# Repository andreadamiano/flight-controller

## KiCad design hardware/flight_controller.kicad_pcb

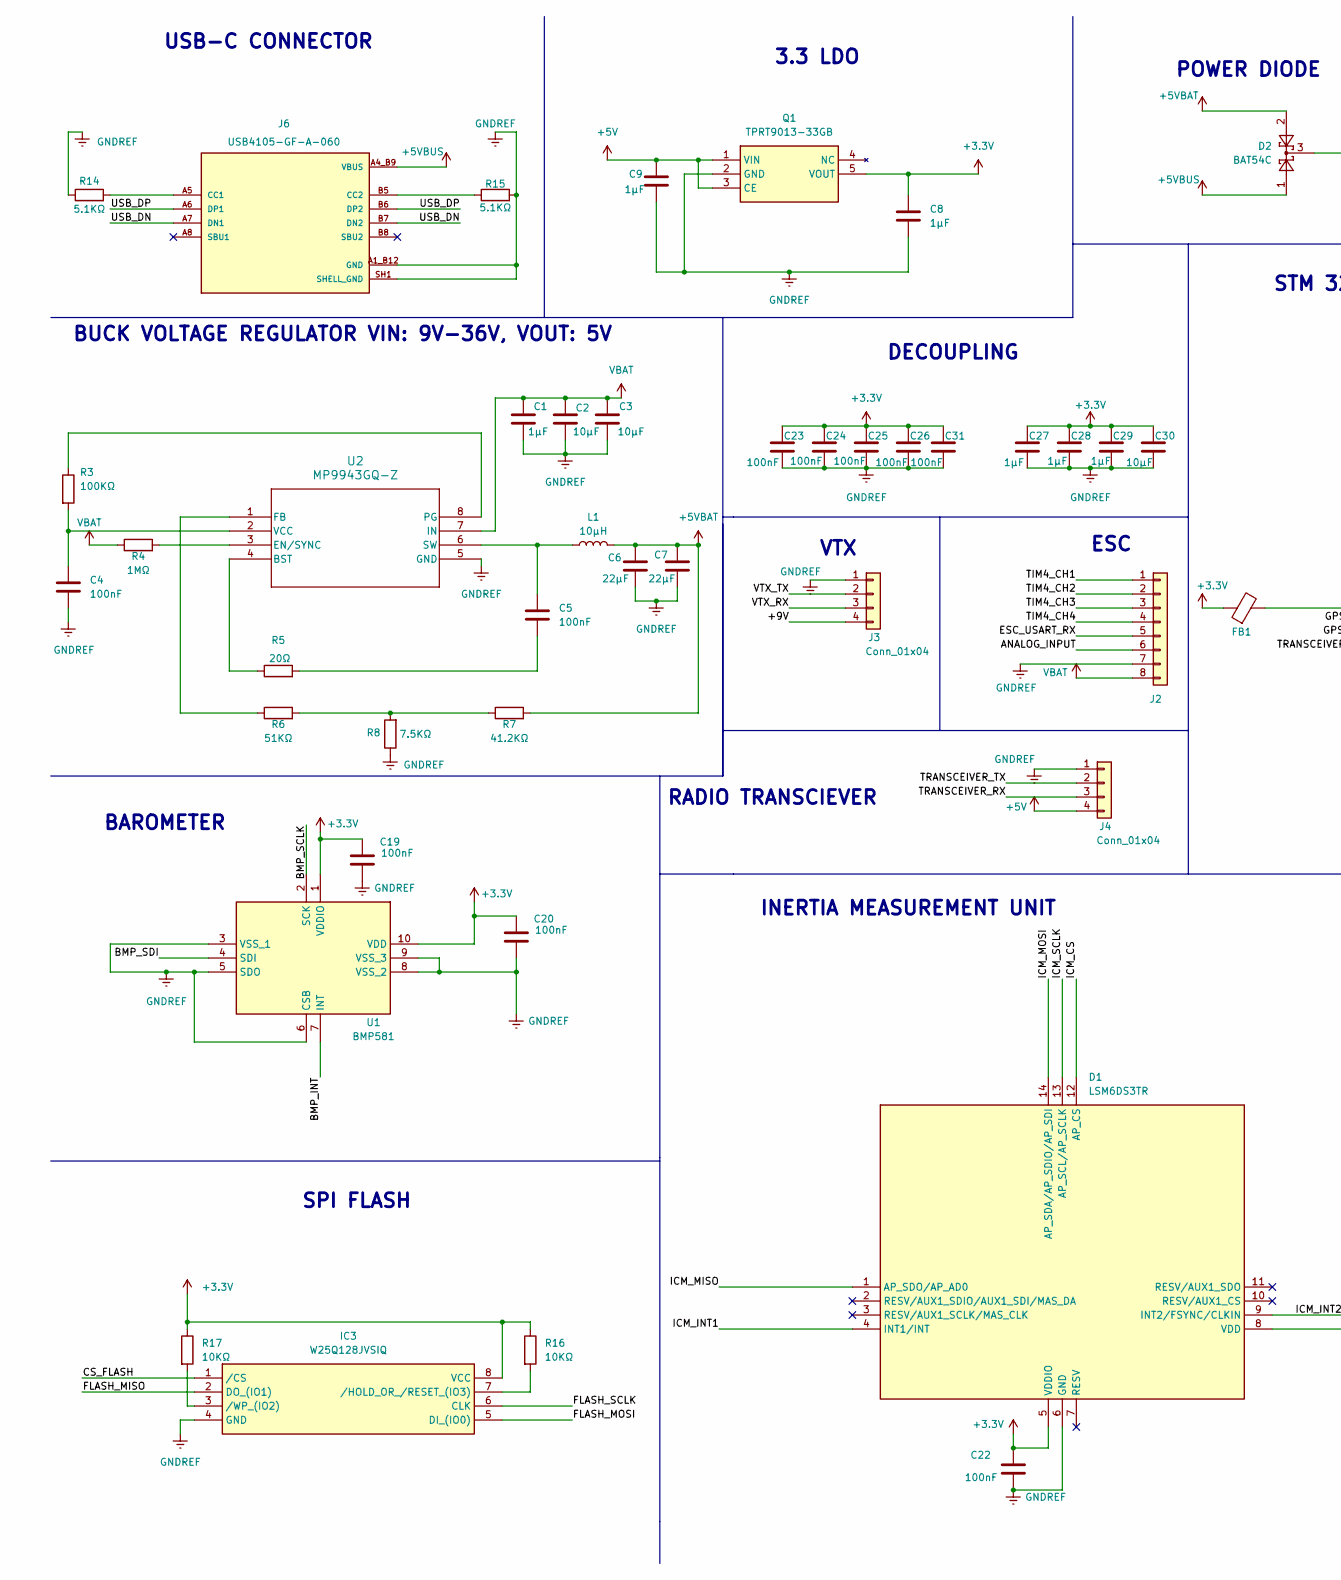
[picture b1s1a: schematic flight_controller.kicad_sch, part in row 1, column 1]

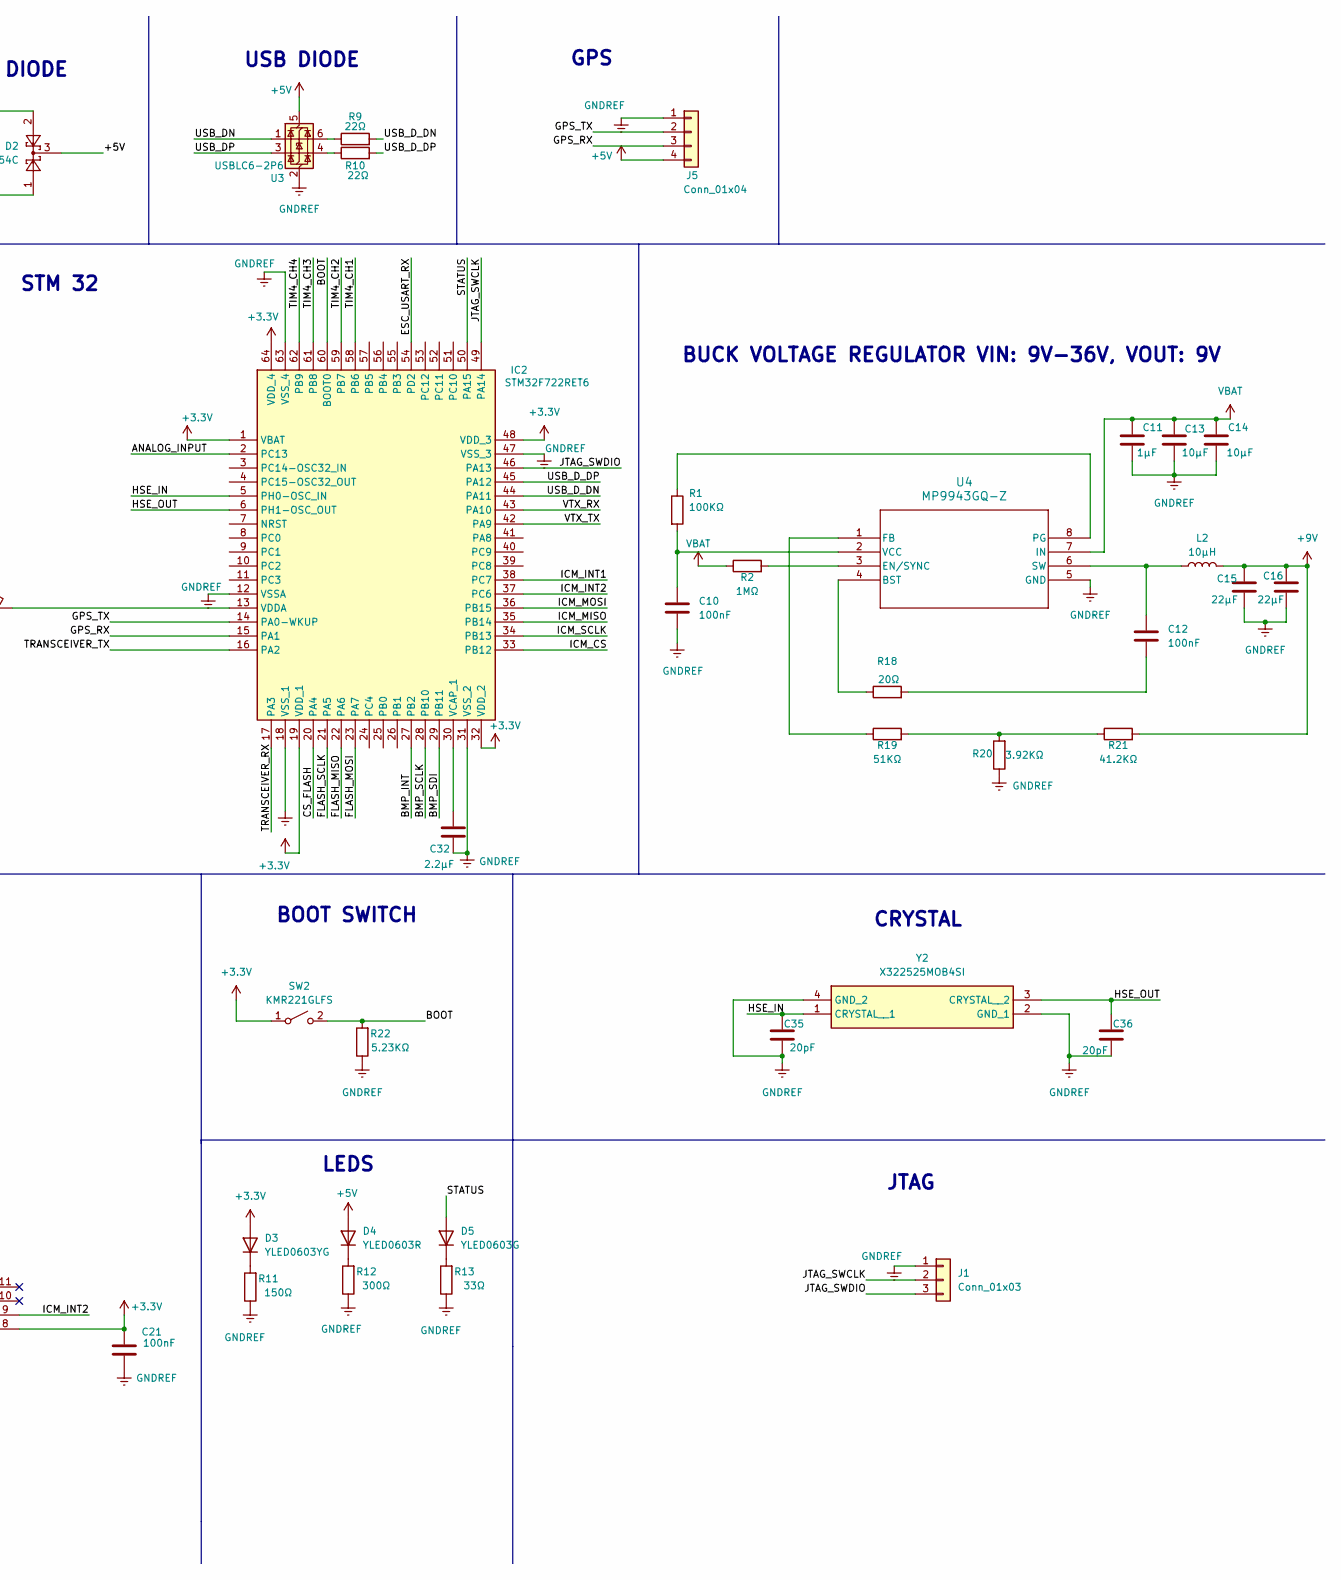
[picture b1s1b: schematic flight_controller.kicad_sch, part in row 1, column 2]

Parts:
C1, C11: 1μF; C_0805_2012Metric
C2, C3, C13, C14, C30: 10μF; C_0805_2012Metric
C4, C5, C10, C12, C19, C20, C21, C22, C23, C24, C25, C26, C31: 100nF; C_0402_1005Metric
C6, C7, C15, C16: 22μF; C_0805_2012Metric
C8, C9, C27, C28, C29: 1μF; C_0603_1608Metric
C32: 2.2μF; C_0603_1608Metric
C35, C36: 20pF; C_0402_1005Metric
D1: LSM6DS3TR; QFN50P300X250X78-14N; Manufacturer_Part_Number ICM-45686
D2: BAT54C; SOT-23
D3: YLED0603YG; LED_0603_1608Metric
D4: YLED0603R; LED_0603_1608Metric
D5: YLED0603G; LED_0603_1608Metric
FB1: FCM1608KF-601T03; L_0603_1608Metric
IC2: STM32F722RET6; QFP50P1200X1200X160-64N; Manufacturer_Part_Number STM32F722RET6; Mouser Part Number 511-STM32F722RET6
IC3: W25Q128JVSIQ; SOIC127P790X216-8N; Manufacturer_Part_Number W25Q128JVSIQ; Mouser Part Number 454-W25Q128JVSIQ
J1: Conn_01x03; PinHeader_1x03_P1.00mm_Vertical
J2: JST SM08B-SRSS-TB(LF)(SN); JST_SH_SM08B-SRSS-TB_1x08-1MP_P1.00mm_Horizontal
J3, J4, J5: Conn_01x04; PinHeader_1x04_P2.54mm_Vertical
J6: USB4105-GF-A-060; GCT_USB4105-GF-A-060; PARTREV B3
L1, L2: 10μH; IND_FXL0530_CMT
Q1: TPRT9013-33GB; SOT95P280X125-5N; Manufacturer_Part_Number TPRT9013-33GB
R1, R3: 100KΩ; R_0402_1005Metric
R2, R4: 1MΩ; R_0603_1608Metric
R5, R18: 20Ω; R_0402_1005Metric
R6, R19: 51KΩ; R_0402_1005Metric
R7, R21: 41.2KΩ; R_0402_1005Metric
R8: 7.5KΩ; R_0402_1005Metric
R9, R10: 22Ω; R_0402_1005Metric
R11: 150Ω; R_0402_1005Metric
R12: 300Ω; R_0402_1005Metric
R13: 33Ω; R_0402_1005Metric
R14, R15: 5.1KΩ; R_0402_1005Metric
R16, R17: 10KΩ; R_0402_1005Metric
R20: 3.92KΩ; R_0402_1005Metric
R22: 5.23KΩ; R_0402_1005Metric
SW2: KMR221GLFS; SW_Push_1P1T-SH_NO_CK_KMR2xxG
U1: BMP581; Manufacturer_Part_Number BMP581; Mouser Part Number 262-BMP581
U2, U4: MP9943GQ-Z; QFN-8_MP9943_MNP
U3: USBLC6-2P6; SOT-666
Y2: X322525MOB4SI; Manufacturer_Part_Number X322525MOB4SI

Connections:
+3.3V: C8.1, C19.1, C20.1, C21.1, C22.1, C23.2, C24.2, C25.2, C26.2, C27.2, C28.2, C29.2, C30.2, C31.2, D1.5 (VDDIO), D1.8 (VDD), D3.2 (A), FB1.1, IC2.1 (VBAT), IC2.19 (VDD_1), IC2.32 (VDD_2), IC2.48 (VDD_3), IC2.64 (VDD_4), IC3.8 (VCC), Q1.5 (VOUT), R16.1, R17.1, SW2.1 (A), U1.1 (VDDIO), U1.10 (VDD)
+5V: C9.1, D2.3, D4.2 (A), J4.4, J5.4, Q1.1 (VIN), Q1.3 (CE), U3.5 (VBUS)
+5VBAT: C6.1, C7.1, D2.2, L1.2, R7.2
+5VBUS: D2.1, J6.A4_B9 (VBUS), J6.B4_A9 (VBUS)
+9V: C15.1, C16.1, J3.4, L2.2, R21.2
/ANALOG_INPUT: IC2.2 (PC13), J2.6
/BMP_INT: IC2.27 (PB2), U1.7 (INT)
/BMP_SCLK: IC2.28 (PB10), U1.2 (SCK)
/BMP_SDI: IC2.29 (PB11), U1.4 (SDI)
/BOOT: IC2.60 (BOOT0), R22.2, SW2.2 (B)
/CS_FLASH: IC2.20 (PA4), IC3.1 (/CS)
/ESC_USART_RX: IC2.54 (PD2), J2.5
/FLASH_MISO: IC2.22 (PA6), IC3.2 (DO_(IO1))
/FLASH_MOSI: IC2.23 (PA7), IC3.5 (DI_(IO0))
/FLASH_SCLK: IC2.21 (PA5), IC3.6 (CLK)
/GPS_RX: IC2.15 (PA1), J5.3
/GPS_TX: IC2.14 (PA0-WKUP), J5.2
/HSE_IN: C35.2, IC2.5 (PH0-OSC_IN), Y2.1 (CRYSTAL__1)
/HSE_OUT: C36.2, IC2.6 (PH1-OSC_OUT), Y2.3 (CRYSTAL__2)
/ICM_CS: D1.12 (AP_CS), IC2.33 (PB12)
/ICM_INT1: D1.4 (INT1/INT), IC2.38 (PC7)
/ICM_INT2: D1.9 (INT2/FSYNC/CLKIN), IC2.37 (PC6)
/ICM_MISO: D1.1 (AP_SDO/AP_AD0), IC2.35 (PB14)
/ICM_MOSI: D1.14 (AP_SDA/AP_SDIO/AP_SDI), IC2.36 (PB15)
/ICM_SCLK: D1.13 (AP_SCL/AP_SCLK), IC2.34 (PB13)
/JTAG_SWCLK: IC2.49 (PA14), J1.2
/JTAG_SWDIO: IC2.46 (PA13), J1.3
/STATUS: D5.2 (A), IC2.50 (PA15)
/TIM4_CH1: IC2.58 (PB6), J2.1
/TIM4_CH2: IC2.59 (PB7), J2.2
/TIM4_CH3: IC2.61 (PB8), J2.3
/TIM4_CH4: IC2.62 (PB9), J2.4
/TRANSCEIVER_RX: IC2.17 (PA3), J4.3
/TRANSCEIVER_TX: IC2.16 (PA2), J4.2
/USB_DN: J6.A7 (DN1), J6.B7 (DN2), U3.1 (I/O1)
/USB_DP: J6.A6 (DP1), J6.B6 (DP2), U3.3 (I/O2)
/USB_D_DN: IC2.44 (PA11), R9.2
/USB_D_DP: IC2.45 (PA12), R10.2
/VTX_RX: IC2.43 (PA10), J3.3
/VTX_TX: IC2.42 (PA9), J3.2
GNDREF: C1.2, C2.2, C3.2, C4.2, C6.2, C7.2, C8.2, C9.2, C10.2, C11.2, C13.2, C14.2, C15.2, C16.2, C19.2, C20.2, C21.2, C22.2, C23.1, C24.1, C25.1, C26.1, C27.1, C28.1, C29.1, C30.1, C31.1, C32.1, C35.1, C36.1, D1.6 (GND), IC2.12 (VSSA), IC2.18 (VSS_1), IC2.31 (VSS_2), IC2.47 (VSS_3), IC2.63 (VSS_4), IC3.4 (GND), J1.1, J2.7, J3.1, J4.1, J5.1, J6.A1_B12 (GND), J6.B1_A12 (GND), J6.SH1 (SHELL_GND), J6.SH2 (SHELL_GND), J6.SH3 (SHELL_GND), J6.SH4 (SHELL_GND), Q1.2 (GND), R8.1, R11.1, R12.1, R13.1, R14.1, R15.2, R20.1, R22.1, U1.3 (VSS_1), U1.5 (SDO), U1.6 (CSB), U1.8 (VSS_2), U1.9 (VSS_3), U2.5 (GND), U3.2 (GND), U4.5 (GND), Y2.2 (GND_1), Y2.4 (GND_2)
unnamed: C5.2, R5.2
unnamed: C12.2, R18.2
unnamed: D3.1 (K), R11.2
unnamed: D4.1 (K), R12.2
unnamed: D5.1 (K), R13.2
unnamed: C32.2, IC2.30 (VCAP_1)
unnamed: FB1.2, IC2.13 (VDDA)
unnamed: IC3.7 (/HOLD_OR_/RESET_(IO3)), R16.2
unnamed: IC3.3 (/WP_(IO2)), R17.2
unnamed: J6.A5 (CC1), R14.2
unnamed: J6.B5 (CC2), R15.1
unnamed: R6.2, R7.1, R8.2
unnamed: R9.1, U3.6 (I/O1)
unnamed: R10.1, U3.4 (I/O2)
unnamed: R19.2, R20.2, R21.1
unnamed: R5.1, U2.4 (BST)
unnamed: R4.2, U2.3 (EN/SYNC)
unnamed: R6.1, U2.1 (FB)
unnamed: R3.1, U2.8 (PG)
unnamed: C5.1, L1.1, U2.6 (SW)
unnamed: C4.1, R3.2, U2.2 (VCC)
unnamed: R18.1, U4.4 (BST)
unnamed: R2.2, U4.3 (EN/SYNC)
unnamed: R19.1, U4.1 (FB)
unnamed: R1.1, U4.8 (PG)
unnamed: C12.1, L2.1, U4.6 (SW)
unnamed: C10.1, R1.2, U4.2 (VCC)
VBAT: C1.1, C2.1, C3.1, C11.1, C13.1, C14.1, J2.8, R2.1, R4.1, U2.7 (IN), U4.7 (IN)

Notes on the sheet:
3.3 LDO
INERTIA MEASUREMENT UNIT
STM 32
CRYSTAL
JTAG
POWER DIODE
ESC
VTX
USB DIODE
DECOUPLING
BUCK VOLTAGE REGULATOR VIN: 9V-36V, VOUT: 9V
BAROMETER
RADIO TRANSCIEVER
GPS
SPI FLASH
USB-C CONNECTOR
BOOT SWITCH
BUCK VOLTAGE REGULATOR VIN: 9V-36V, VOUT: 5V
LEDS

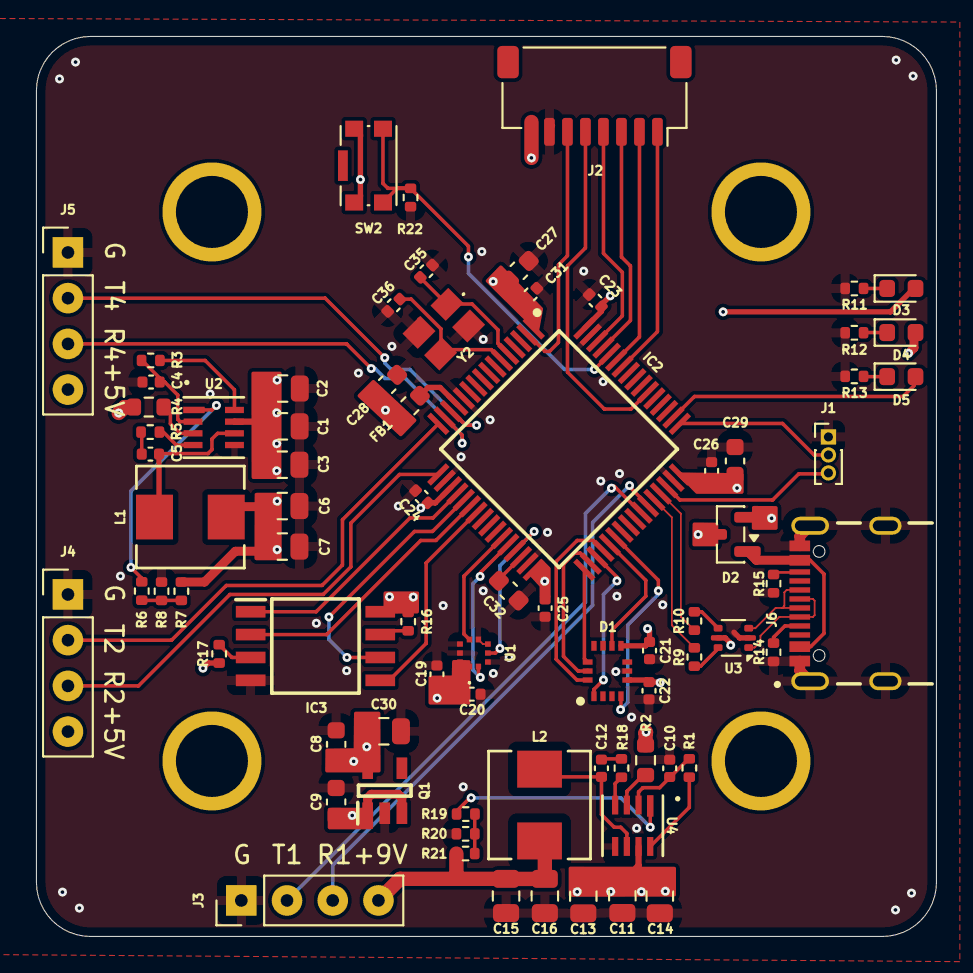
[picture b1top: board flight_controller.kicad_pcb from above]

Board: 6 copper layers, 50.0 x 50.0 mm, 77 parts (0 on the bottom side), 69 nets.

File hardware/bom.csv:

Id,Designator,Footprint,Quantity,Designation,Supplier and ref
1,"U4,U2",QFN-8_MP9943_MNP,2,MP9943GQ-Z,C51889390
2,"C10,C22,C4,C12,C20,C26,C5,C24,C23,C31,C21,C19,C25",C_0402_1005Metric,13,100nF,C60474
3,"R1,R4,R3,R2",R_0402_1005Metric,4,100KΩ,C60491
4,"R18,R5",R_0402_1005Metric,2,20Ω,C138031
5,"R14,R15",R_0402_1005Metric,2,5.1KΩ,C105872
6,IC2,QFP50P1200X1200X160-64N,1,STM32F722RET6,C118207
7,R22,R_0402_1005Metric,1,5.23KΩ,C852857
8,"R21,R7",R_0402_1005Metric,2,41.2KΩ,C844310
9,R20,R_0402_1005Metric,1,3.92KΩ,C137988
10,"R19,R6",R_0402_1005Metric,2,51KΩ,C107229
11,"R17,R16",R_0402_1005Metric,2,10KΩ,C60490
12,R13,R_0402_1005Metric,1,33Ω,C138002
13,R12,R_0402_1005Metric,1,300Ω,C2930000
14,R11,R_0402_1005Metric,1,150Ω,C2909321
15,"R10,R9",R_0402_1005Metric,2,22Ω,C114765
16,R8,R_0402_1005Metric,1,7.5KΩ,C25918
17,"C32,C29,C28,C27,C9,C8",C_0603_1608Metric,6,1μF,C15849
18,"C30,C3,C11,C13,C14,C1,C2",C_0805_2012Metric,7,10μF,C95841
19,SW2,SW_Push_1P1T-SH_NO_CK_KMR2xxG,1,KMR221GLFS,C72443
20,J6,GCT_USB4105-GF-A-060,1,USB4105-GF-A-060,C3025063
21,J2,JST_SH_SM08B-SRSS-TB_1x08-1MP_P1.00mm_Horizontal,1,JST SM08B-SRSS-TB(LF)(SN),C160407
22,D3,LED_0603_1608Metric,1,YLED0603YG,C19171392
23,"C15,C7,C6,C16",C_0805_2012Metric,4,22μF,C602037
24,"C35,C36",C_0402_1005Metric,2,20pF,C107000
25,D4,LED_0603_1608Metric,1,YLED0603R,C19171390
26,IC3,SOIC127P790X216-8N,1,W25Q128JVSIQ,C97521
27,"L2,L1",IND_FXL0530_CMT,2,10μH,C181721
28,D1,QFN50P300X250X78-14N,1,ICM-45686,C22459454
29,U3,SOT-666,1,USBLC6-2P6,C15999
30,FB1,L_0603_1608Metric,1,FCM1608KF-601T03,C141723
31,Y2,X322525MOB4SI,1,X322525MOB4SI,C9006
32,U1,BMP581,1,BMP581,C5362283
33,Q1,SOT95P280X125-5N,1,TPRT9013-33GB,C587158
34,D5,LED_0603_1608Metric,1,YLED0603G,C19273151
35,D2,SOT-23,1,BAT54C,C916424

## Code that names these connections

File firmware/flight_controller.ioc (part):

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Mcu.Name=STM32F722R(C-E)Tx
Mcu.Package=LQFP64
Mcu.UserName=STM32F722RETx
PA0-WKUP.Mode=Asynchronous
PA0-WKUP.Signal=UART4_TX
PA1.Mode=Asynchronous
PA1.Signal=UART4_RX
PA10.Mode=Asynchronous
PA10.Signal=USART1_RX
PA11.Mode=Host_Only
PA11.Signal=USB_OTG_FS_DM
PA12.Mode=Host_Only
PA12.Signal=USB_OTG_FS_DP
PA13.Mode=Serial_Wire
PA13.Signal=SYS_JTMS-SWDIO
PA14.Mode=Serial_Wire
PA14.Signal=SYS_JTCK-SWCLK
PA2.Mode=Asynchronous
PA2.Signal=USART2_TX
PA3.Mode=Asynchronous
PA3.Signal=USART2_RX
PA4.GPIOParameters=GPIO_Label
PA4.GPIO_Label=CS_FLASH
PA4.Signal=GPIO_Output
PA5.Mode=Full_Duplex_Master
PA5.Signal=SPI1_SCK
PA6.Mode=Full_Duplex_Master
PA6.Signal=SPI1_MISO
PA7.Mode=Full_Duplex_Master
PA7.Signal=SPI1_MOSI
PA8.GPIOParameters=GPIO_Label
PA8.GPIO_Label=STATUS
PA8.Signal=GPIO_Output
PA9.Mode=Asynchronous
PA9.Signal=USART1_TX
PB10.Mode=I2C
PB10.Signal=I2C2_SCL
PB11.Mode=I2C
PB11.Signal=I2C2_SDA
PB12.Mode=NSS_Signal_Hard_Output
PB12.Signal=SPI2_NSS
PB13.Mode=Full_Duplex_Master
PB13.Signal=SPI2_SCK
PB14.Mode=Full_Duplex_Master
PB14.Signal=SPI2_MISO
PB15.Mode=Full_Duplex_Master
PB15.Signal=SPI2_MOSI
PB2.GPIOParameters=GPIO_Label
PB2.GPIO_Label=BMP_INT
PB2.Signal=GPXTI2
PB6.Signal=S_TIM4_CH1
PB7.Signal=S_TIM4_CH2
PB8.Signal=S_TIM4_CH3
PB9.Signal=S_TIM4_CH4
PC12.Mode=Asynchronous
PC12.Signal=UART5_TX
PC13.GPIOParameters=GPIO_Label
PC13.GPIO_Label=ANALOG_INPUT
PC13.Signal=GPIO_Analog
PC6.GPIOParameters=GPIO_Label
PC6.GPIO_Label=ICM_INT2
PC6.Signal=GPXTI6
PC7.GPIOParameters=GPIO_Label
PC7.GPIO_Label=ICM_INT1
PC7.Signal=GPXTI7
PD2.Mode=Asynchronous
PD2.Signal=UART5_RX
PH0-OSC_IN.Mode=HSE-External-Oscillator
PH0-OSC_IN.Signal=RCC_OSC_IN
PH1-OSC_OUT.Mode=HSE-External-Oscillator
PH1-OSC_OUT.Signal=RCC_OSC_OUT
RCC.HSE_VALUE=25000000
board=custom

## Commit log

2026-04-27 electric schematic
2026-04-27 pinout
2026-04-27 stm32
2026-05-12 changed components
2026-05-13 interfaces
2026-05-18 stm32 interfaces
2026-05-18 footprints
2026-05-18 pcb cut
2026-05-19 layout
2026-05-21 resized board
2026-05-30 redefined signal layout
2026-05-31 power planes
2026-05-31 stackup
2026-05-31 differential pair
2026-06-01 fix errors
2026-06-01 resizing
2026-06-02 production
2026-06-02 removed backup folder
2026-06-02 .gitignore
2026-06-02 crystal oscillator
2026-06-02 silkscreen
2026-06-03 jtag interface
2026-06-03 resolved errors
2026-06-03 copper pour
2026-06-03 component position
2026-06-07 via size
2026-06-08 boot button
2026-06-08 production files
2026-06-08 mounting holes
2026-06-10 resized holes
2026-06-11 docs
2026-06-11 changed capacitor
2026-06-11 changed bom
2026-06-14 added via ground
2026-06-15 power polygons
2026-06-27 picture
